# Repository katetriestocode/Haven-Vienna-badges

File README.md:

# Haven Vienna badges

Super duper cool badges for the Haven Vienna event on Nov. 14th 2026!

## Design

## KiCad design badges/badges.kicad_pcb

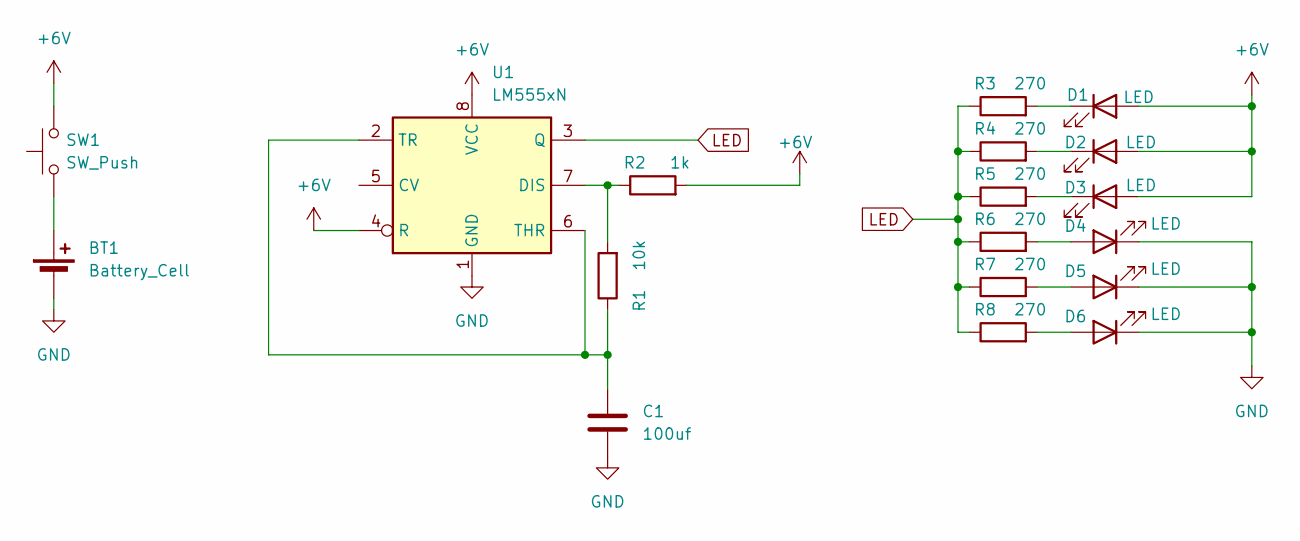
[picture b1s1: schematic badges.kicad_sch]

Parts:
BT1: Battery_Cell; BatteryHolder_MYOUNG_BS-07-A1BJ001_CR2032
C1: 100uf; C_Radial_D6.3mm_H5.0mm_P2.50mm
D1, D2, D3, D4, D5, D6: LED; LED_D5.0mm
R1: 10k; R_Axial_DIN0207_L6.3mm_D2.5mm_P7.62mm_Horizontal
R2: 1k; R_Axial_DIN0207_L6.3mm_D2.5mm_P7.62mm_Horizontal
R3, R4, R5, R6, R7, R8: 270; R_Axial_DIN0207_L6.3mm_D2.5mm_P7.62mm_Horizontal
SW1: SW_Push; SW_PUSH_6mm
U1: LM555xN; DIP-8_W7.62mm

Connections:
+6V: D1.2 (A), D2.2 (A), D3.2 (A), R2.2, SW1.2, U1.4 (R), U1.8 (VCC)
GND: BT1.2 (-), C1.2, D4.1 (K), D5.1 (K), D6.1 (K), U1.1 (GND)
LED: R3.1, R4.1, R5.1, R6.1, R7.1, R8.1, U1.3 (Q)
unnamed: BT1.1 (+), SW1.1
unnamed: D1.1 (K), R3.2
unnamed: D2.1 (K), R4.2
unnamed: D3.1 (K), R5.2
unnamed: D4.2 (A), R6.2
unnamed: D5.2 (A), R7.2
unnamed: D6.2 (A), R8.2
unnamed: R1.2, R2.1, U1.7 (DIS)
unnamed: C1.1, R1.1, U1.2 (TR), U1.6 (THR)

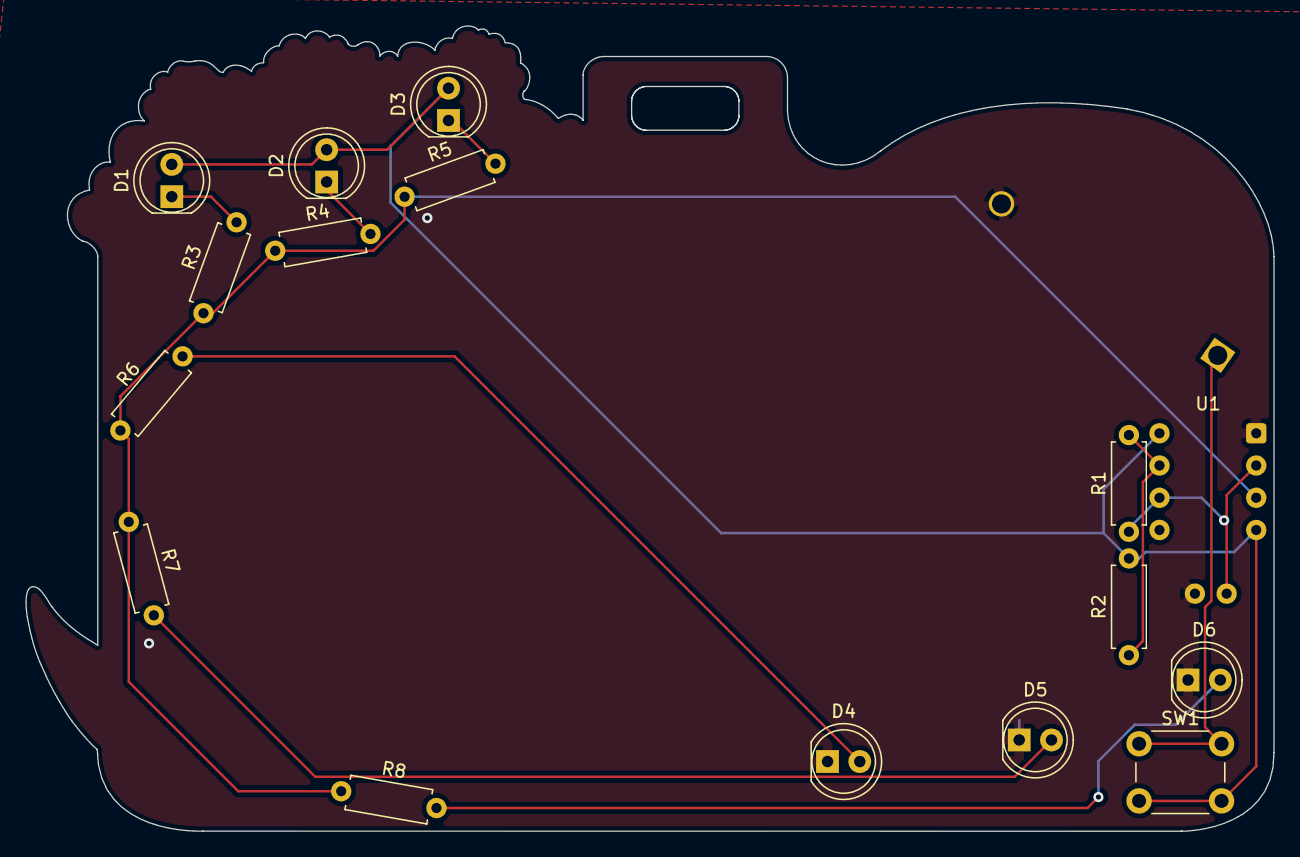
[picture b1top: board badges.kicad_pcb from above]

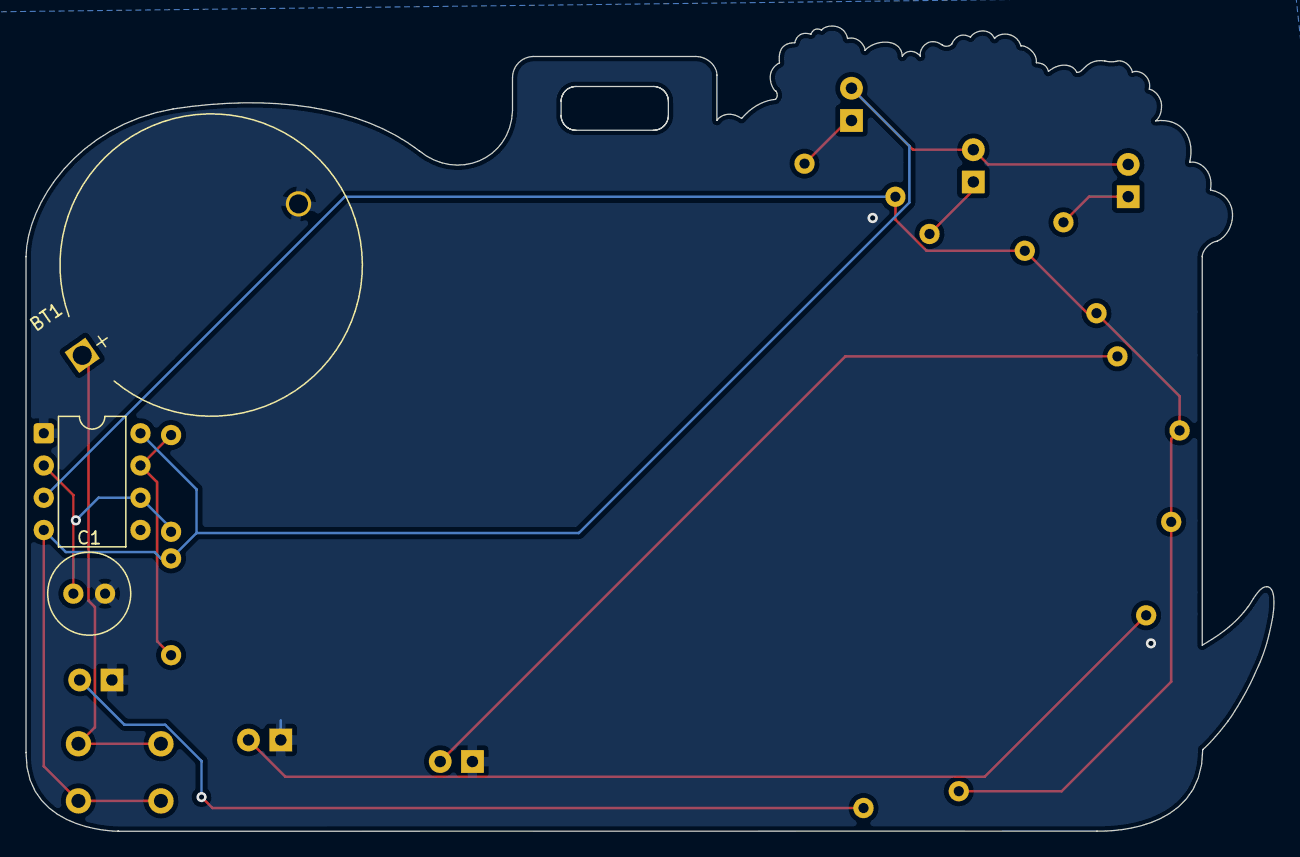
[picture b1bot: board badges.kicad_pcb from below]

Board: 2 copper layers, 98.3 x 63.4 mm, 18 parts (3 on the bottom side), 12 nets.
